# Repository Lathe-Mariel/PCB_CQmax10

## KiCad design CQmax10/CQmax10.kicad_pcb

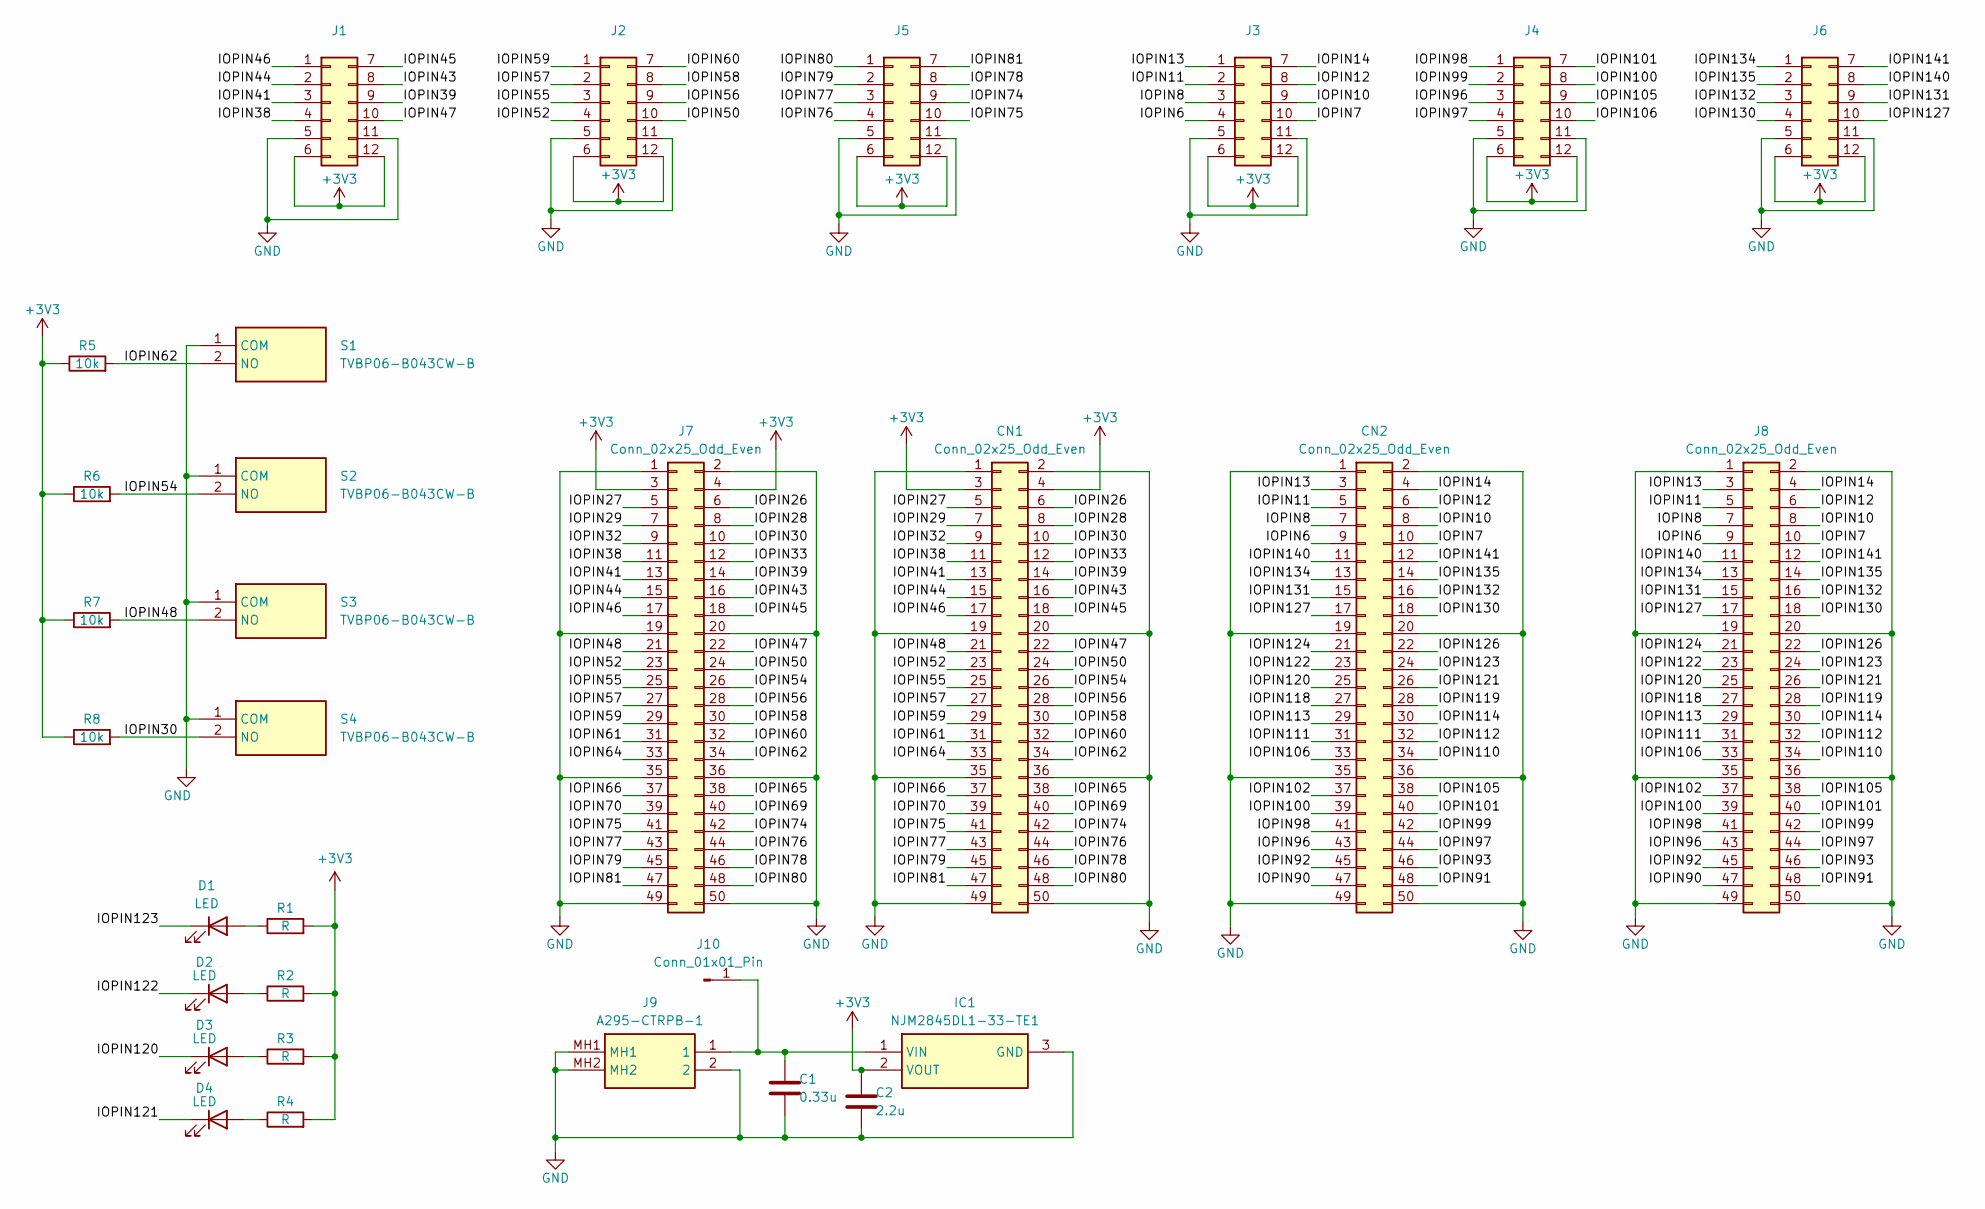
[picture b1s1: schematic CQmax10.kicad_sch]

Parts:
C1: 0.33u; C_0603_1608Metric_Pad1.08x0.95mm_HandSolder
C2: 2.2u; C_0603_1608Metric_Pad1.08x0.95mm_HandSolder
CN1, CN2: Conn_02x25_Odd_Even; PinSocket_2x25_P2.54mm_Vertical
D1, D2, D3, D4: LED; LED_0603_1608Metric_Pad1.05x0.95mm_HandSolder
IC1: NJM2845DL1-33-TE1; TO-252-3-L1; Manufacturer_Part_Number NJM2845DL1-33-TE1
J1, J2, J3, J4, J5, J6: Pmod_socket
J7, J8: Conn_02x25_Odd_Even; PinHeader_2x25_P2.54mm_Vertical
J9: A295-CTRPB-1; A295CTRPB1; Manufacturer_Part_Number A295-CTRPB-1
J10: Conn_01x01_Pin; PinHeader_1x01_P2.54mm_Vertical
R1, R2, R3, R4: R; R_0603_1608Metric_Pad0.98x0.95mm_HandSolder
R5, R6, R7, R8: 10k; R_0603_1608Metric_Pad0.98x0.95mm_HandSolder
S1, S2, S3, S4: TVBP06-B043CW-B; TVBP06B043CWB; Manufacturer_Part_Number TVBP06-B043CW-B

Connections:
+3V3: C2.1, CN1.3, CN1.4, IC1.2 (VOUT), J1.6, J1.12, J2.6, J2.12, J3.6, J3.12, J4.6, J4.12, J5.6, J5.12, J6.6, J6.12, J7.3, J7.4, R1.2, R2.2, R3.2, R4.2, R5.1, R6.1, R7.1, R8.1
/IOPIN6: CN2.9, J3.4, J8.9
/IOPIN7: CN2.10, J3.10, J8.10
/IOPIN8: CN2.7, J3.3, J8.7
/IOPIN10: CN2.8, J3.9, J8.8
/IOPIN11: CN2.5, J3.2, J8.5
/IOPIN12: CN2.6, J3.8, J8.6
/IOPIN13: CN2.3, J3.1, J8.3
/IOPIN14: CN2.4, J3.7, J8.4
/IOPIN26: CN1.6, J7.6
/IOPIN27: CN1.5, J7.5
/IOPIN28: CN1.8, J7.8
/IOPIN29: CN1.7, J7.7
/IOPIN30: CN1.10, J7.10, R8.2, S4.2 (NO)
/IOPIN32: CN1.9, J7.9
/IOPIN33: CN1.12, J7.12
/IOPIN38: CN1.11, J1.4, J7.11
/IOPIN39: CN1.14, J1.9, J7.14
/IOPIN41: CN1.13, J1.3, J7.13
/IOPIN43: CN1.16, J1.8, J7.16
/IOPIN44: CN1.15, J1.2, J7.15
/IOPIN45: CN1.18, J1.7, J7.18
/IOPIN46: CN1.17, J1.1, J7.17
/IOPIN47: CN1.22, J1.10, J7.22
/IOPIN48: CN1.21, J7.21, R7.2, S3.2 (NO)
/IOPIN50: CN1.24, J2.10, J7.24
/IOPIN52: CN1.23, J2.4, J7.23
/IOPIN54: CN1.26, J7.26, R6.2, S2.2 (NO)
/IOPIN55: CN1.25, J2.3, J7.25
/IOPIN56: CN1.28, J2.9, J7.28
/IOPIN57: CN1.27, J2.2, J7.27
/IOPIN58: CN1.30, J2.8, J7.30
/IOPIN59: CN1.29, J2.1, J7.29
/IOPIN60: CN1.32, J2.7, J7.32
/IOPIN61: CN1.31, J7.31
/IOPIN62: CN1.34, J7.34, R5.2, S1.2 (NO)
/IOPIN64: CN1.33, J7.33
/IOPIN65: CN1.38, J7.38
/IOPIN66: CN1.37, J7.37
/IOPIN69: CN1.40, J7.40
/IOPIN70: CN1.39, J7.39
/IOPIN74: CN1.42, J5.9, J7.42
/IOPIN75: CN1.41, J5.10, J7.41
/IOPIN76: CN1.44, J5.4, J7.44
/IOPIN77: CN1.43, J5.3, J7.43
/IOPIN78: CN1.46, J5.8, J7.46
/IOPIN79: CN1.45, J5.2, J7.45
/IOPIN80: CN1.48, J5.1, J7.48
/IOPIN81: CN1.47, J5.7, J7.47
/IOPIN90: CN2.47, J8.47
/IOPIN91: CN2.48, J8.48
/IOPIN92: CN2.45, J8.45
/IOPIN93: CN2.46, J8.46
/IOPIN96: CN2.43, J4.3, J8.43
/IOPIN97: CN2.44, J4.4, J8.44
/IOPIN98: CN2.41, J4.1, J8.41
/IOPIN99: CN2.42, J4.2, J8.42
/IOPIN100: CN2.39, J4.8, J8.39
/IOPIN101: CN2.40, J4.7, J8.40
/IOPIN102: CN2.37, J8.37
/IOPIN105: CN2.38, J4.9, J8.38
/IOPIN106: CN2.33, J4.10, J8.33
/IOPIN110: CN2.34, J8.34
/IOPIN111: CN2.31, J8.31
/IOPIN112: CN2.32, J8.32
/IOPIN113: CN2.29, J8.29
/IOPIN114: CN2.30, J8.30
/IOPIN118: CN2.27, J8.27
/IOPIN119: CN2.28, J8.28
/IOPIN120: CN2.25, D3.1 (K), J8.25
/IOPIN121: CN2.26, D4.1 (K), J8.26
/IOPIN122: CN2.23, D2.1 (K), J8.23
/IOPIN123: CN2.24, D1.1 (K), J8.24
/IOPIN124: CN2.21, J8.21
/IOPIN126: CN2.22, J8.22
/IOPIN127: CN2.17, J6.10, J8.17
/IOPIN130: CN2.18, J6.4, J8.18
/IOPIN131: CN2.15, J6.9, J8.15
/IOPIN132: CN2.16, J6.3, J8.16
/IOPIN134: CN2.13, J6.1, J8.13
/IOPIN135: CN2.14, J6.2, J8.14
/IOPIN140: CN2.11, J6.8, J8.11
/IOPIN141: CN2.12, J6.7, J8.12
GND: C1.2, C2.2, CN1.1, CN1.2, CN1.19, CN1.20, CN1.35, CN1.36, CN1.49, CN1.50, CN2.1, CN2.2, CN2.19, CN2.20, CN2.35, CN2.36, CN2.49, CN2.50, IC1.3 (GND), J1.5, J1.11, J2.5, J2.11, J3.5, J3.11, J4.5, J4.11, J5.5, J5.11, J6.5, J6.11, J7.1, J7.2, J7.19, J7.20, J7.35, J7.36, J7.49, J7.50, J8.1, J8.2, J8.19, J8.20, J8.35, J8.36, J8.49, J8.50, J9.2, J9.MH1, J9.MH2, S1.1 (COM), S2.1 (COM), S3.1 (COM), S4.1 (COM)
unnamed: D1.2 (A), R1.1
unnamed: D2.2 (A), R2.1
unnamed: D3.2 (A), R3.1
unnamed: D4.2 (A), R4.1
unnamed: C1.1, IC1.1 (VIN), J9.1, J10.1

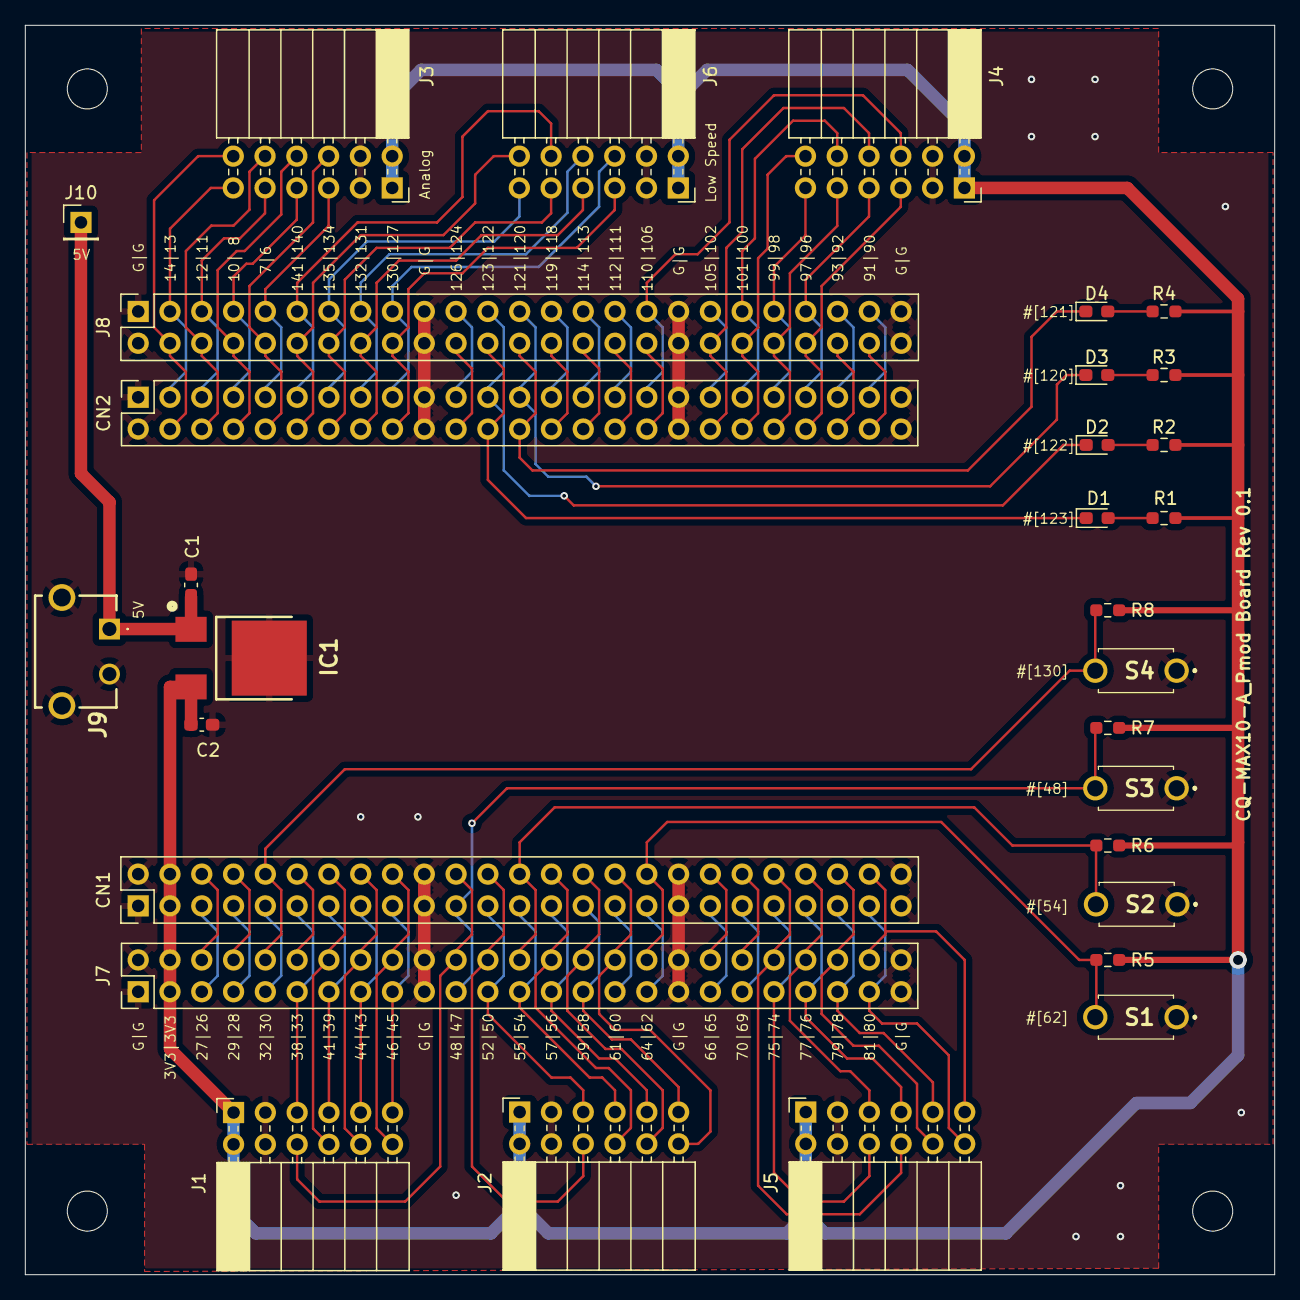
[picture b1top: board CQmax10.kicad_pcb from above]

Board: 2 copper layers, 99.8 x 99.8 mm, 31 parts (0 on the bottom side), 89 nets.

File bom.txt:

# BoM

型式 | 部品
---|--- 
A295-CTRPB-1 | USB TypeC レセプタクル（電源2ピンonly）
NJM2845DL1-33-TE1 | 3.3V Regulater
TVBP06-B043CW-B | Push Switch
 | LED 1608
 | Register 10k 1608
